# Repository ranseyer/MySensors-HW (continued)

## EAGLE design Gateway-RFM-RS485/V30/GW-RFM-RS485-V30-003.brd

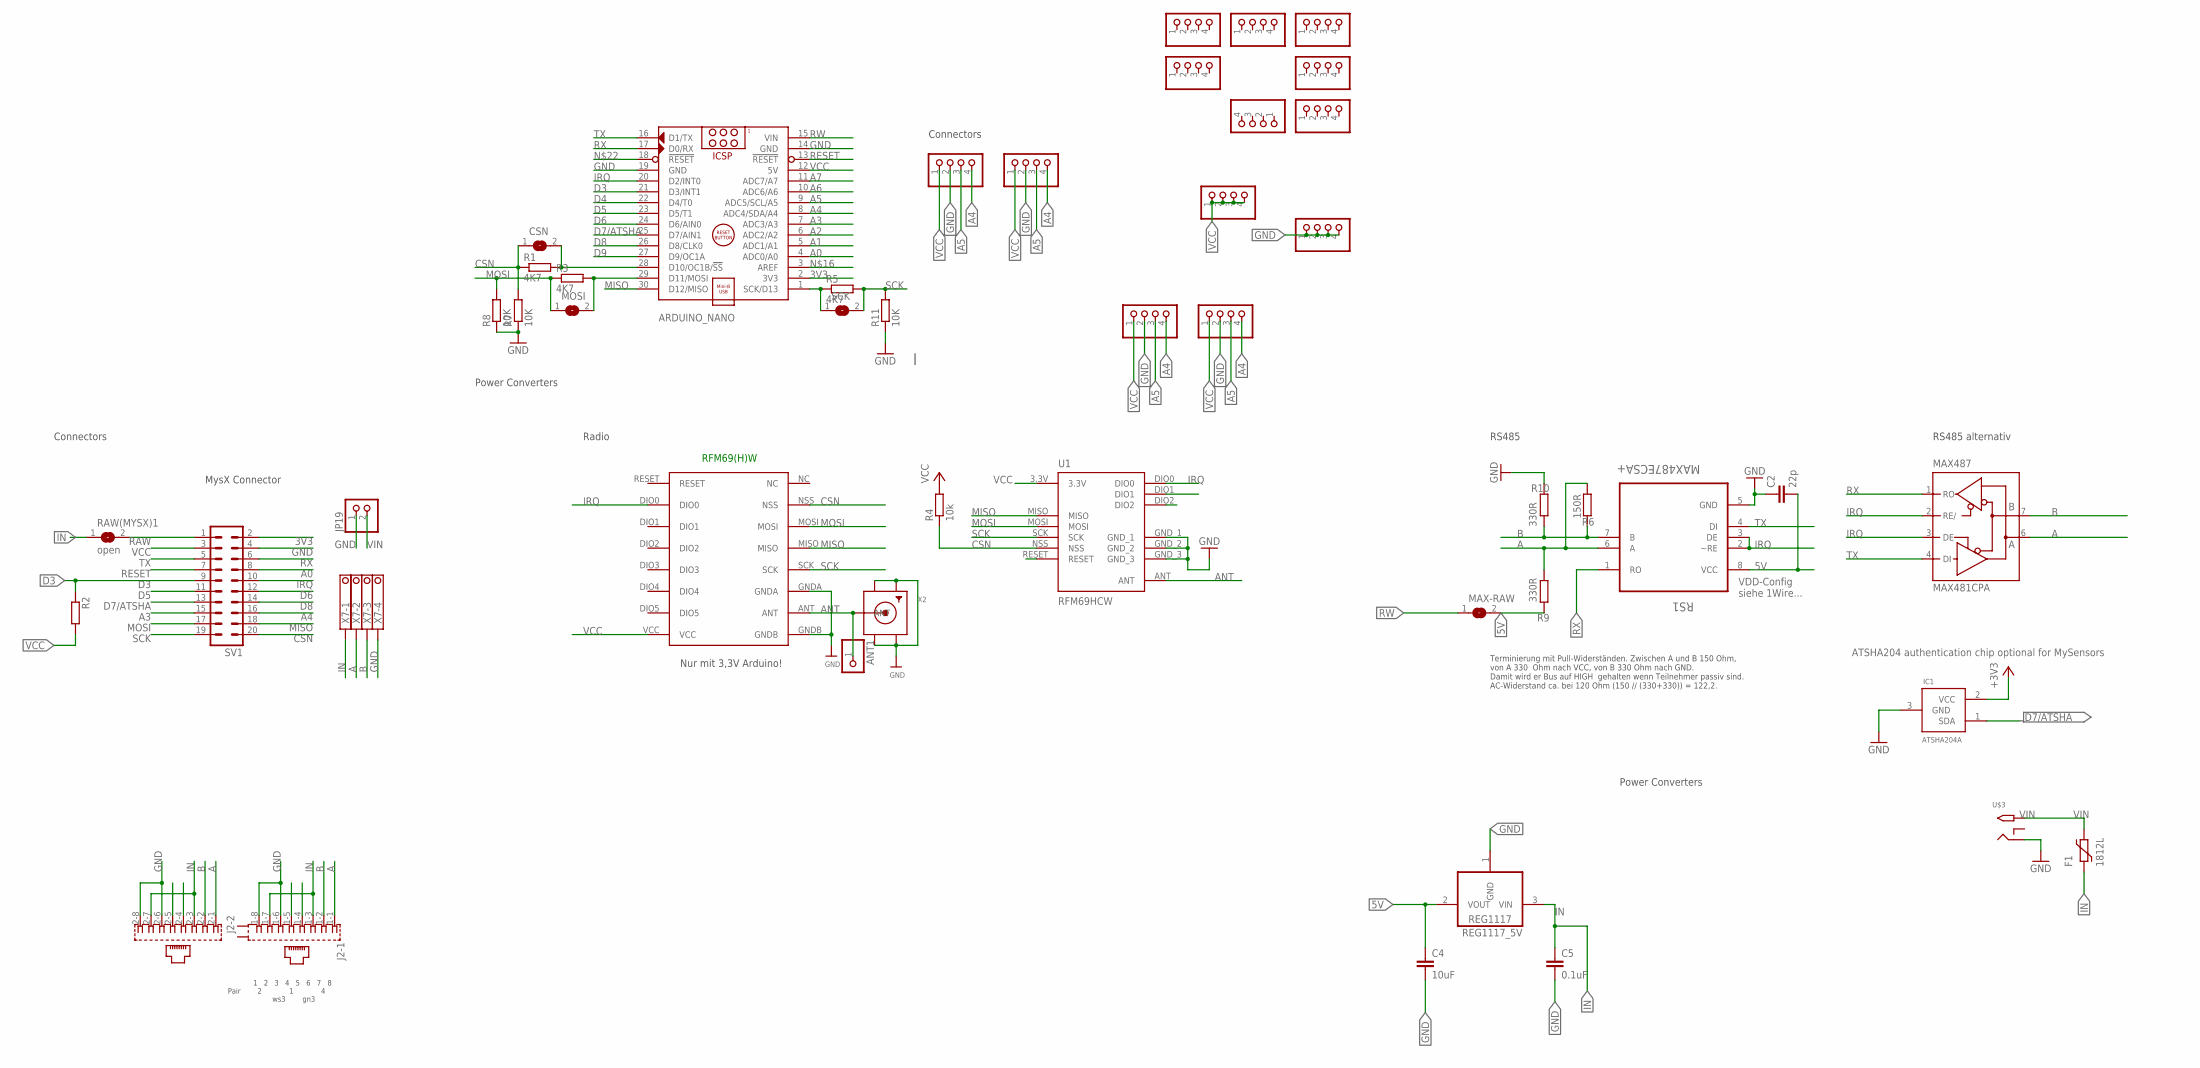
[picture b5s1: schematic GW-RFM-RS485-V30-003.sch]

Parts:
ANT1: PINHD-1X1; 1X01
ARDUINO_NANO: ARDUINO_NANO_OHNE-BOHR; ARDUINO_NANO
C2: 22p; C0805
C4: 10uF; C1210
C5: 0.1uF; C1206
CSN: SJ
F1: 1812L
IC1: ATSHA204A; SOT23
J2: 557570-1
JP1, JP2, JP3, JP4, JP5, JP6, JP7, JP10, JP11, JP12, JP15, JP17, JP18: PINHD-1X04_2.54-S; 1X04-S
JP19: PINHD-1X2; 1X02
MAX487: MAX481CPA; DIL08
MAX-RAW: SJ
MOSI: SJ
R1, R3, R5: 4K7; M0805
R2: R-EU_R0805; R0805
R4: 10k; M0805
R6: 150R; R0805
R7, R8, R11: 10K; M0805
R9, R10: 330R; R0805
RAW(MYSX)1: open; SJ
REG1117_5V: REG1117; SOT223
RFM69W: RFM69HW; RFM
RS1: MAX487ECSA+; SOIC127P600X175-8N
SCK: SJ
SV1: MA10-2
U1: RFM69HCW; RFM69HCW-XXXS2
U$3: 2.1MMJACKTHM; PJ-102A
X2: SMACONNECTOR_EDGE; SMA_EDGELAUNCH
X7: 1751264

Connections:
3V3: ARDUINO_NANO.2 (3V3), SV1.2
5V: C2.2, C4.1, MAX-RAW.2, R9.1, REG1117_5V.2 (VOUT), RS1.8 (VCC)
A: J2.1-1 (1), J2.2-1 (1), MAX487.6 (A), R6.1, R9.2, RS1.6 (A), X7.2
A0: ARDUINO_NANO.4 (ADC0/A0), SV1.8
A1: ARDUINO_NANO.5 (ADC1/A1)
A2: ARDUINO_NANO.6 (ADC2/A2)
A3: ARDUINO_NANO.7 (ADC3/A3), SV1.15
A4: ARDUINO_NANO.8 (ADC4/SDA/A4), JP6.4, JP10.4, JP17.4, JP18.4, SV1.16
A5: ARDUINO_NANO.9 (ADC5/SCL/A5), JP6.3, JP10.3, JP17.3, JP18.3
A6: ARDUINO_NANO.10 (ADC6/A6)
A7: ARDUINO_NANO.11 (ADC7/A7)
ANT: ANT1.1, RFM69W.ANT, U1.ANT, X2.P (ANT)
B: J2.1-2 (2), J2.2-2 (2), MAX487.7 (B), R6.2, R10.1, RS1.7 (B), X7.3
CSN: CSN.1, R1.1, R4.1, R7.2, RFM69W.NSS, SV1.20, U1.NSS
D3: ARDUINO_NANO.21 (D3/INT1), R2.1, SV1.9
D4: ARDUINO_NANO.22 (D4/T0)
D5: ARDUINO_NANO.23 (D5/T1), SV1.11
D6: ARDUINO_NANO.24 (D6/AIN0), SV1.12
D7/ATSHA: ARDUINO_NANO.25 (D7/AIN1), IC1.1 (SDA), SV1.13
D8: ARDUINO_NANO.26 (D8/CLK0), SV1.14
D9: ARDUINO_NANO.27 (D9/OC1A)
GND: ARDUINO_NANO.14 (GND), ARDUINO_NANO.19 (GND), C2.1, C4.2, C5.2, IC1.3 (GND), J2.1-6 (6), J2.1-8 (8), J2.2-6 (6), J2.2-8 (8), JP1.1, JP1.2, JP1.3, JP1.4, JP6.2, JP10.2, JP17.2, JP18.2, JP19.1, MAX487.5 (GND), R7.1, R8.1, R10.2, R11.1, REG1117_5V.1 (GND), RFM69W.GNDA, RFM69W.GNDB, RS1.5 (GND), SV1.4, U1.GND_1, U1.GND_2, U1.GND_3, U$3.RING, X2.GND@1 (GND4), X2.GND@2 (GND3), X2.GND@3 (GND2), X2.GND@4 (GND1), X7.4
IN: C5.1, F1.P$1 (1), J2.1-3 (3), J2.1-7 (7), J2.2-3 (3), J2.2-7 (7), RAW(MYSX)1.1, REG1117_5V.3 (VIN), X7.1
IRQ: ARDUINO_NANO.20 (D2/INT0), RFM69W.DIO0, RS1.2 (~RE), RS1.3 (DE), SV1.10, U1.DIO0
MISO: ARDUINO_NANO.30 (D12/MISO), RFM69W.MISO, SV1.18, U1.MISO
MOSI: MOSI.1, R3.1, R8.2, RFM69W.MOSI, SV1.17, U1.MOSI
unnamed: ARDUINO_NANO.1 (SCK/D13), R5.1, SCK.1
unnamed: ARDUINO_NANO.28 (D10/OC1B/!SS), CSN.2, R1.2
unnamed: ARDUINO_NANO.29 (D11/MOSI), MOSI.2, R3.2
RAW: RAW(MYSX)1.2, SV1.1
RESET: ARDUINO_NANO.13 (!RESET), SV1.7
RW: ARDUINO_NANO.15 (VIN), MAX-RAW.1
RX: ARDUINO_NANO.17 (D0/RX), RS1.1 (RO), SV1.6
SCK: R5.2, R11.2, RFM69W.SCK, SCK.2, SV1.19, U1.SCK
TX: ARDUINO_NANO.16 (D1/TX), RS1.4 (DI), SV1.5
VCC: ARDUINO_NANO.12 (5V), IC1.2 (VCC), JP3.1, JP3.2, JP3.3, JP3.4, JP6.1, JP10.1, JP17.1, JP18.1, MAX487.8 (VCC), R2.2, R4.2, RFM69W.VCC, SV1.3, U1.3.3V
VIN: F1.P$2 (2), JP19.2, U$3.TIP

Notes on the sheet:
RFM69(H)W
Nur mit 3,3V Arduino!
Radio
1 2 3 4 5 6 7 8 Pair 2 1 4 ws3 gn3
Power Converters
ATSHA204 authentication chip optional for MySensors
RS485
VDD-Config siehe 1Wire...
Terminierung mit Pull-Widerständen. Zwischen A und B 150 Ohm, von A 330 Ohm nach VCC, von B 330 Ohm nach GND. Damit wird er Bus auf HIGH gehalten wenn Teilnehmer passiv sind. AC-Widerstand ca. bei 120 Ohm (150 // (330+330)) = 122,2.
RS485 alternativ
Connectors
MysX Connector

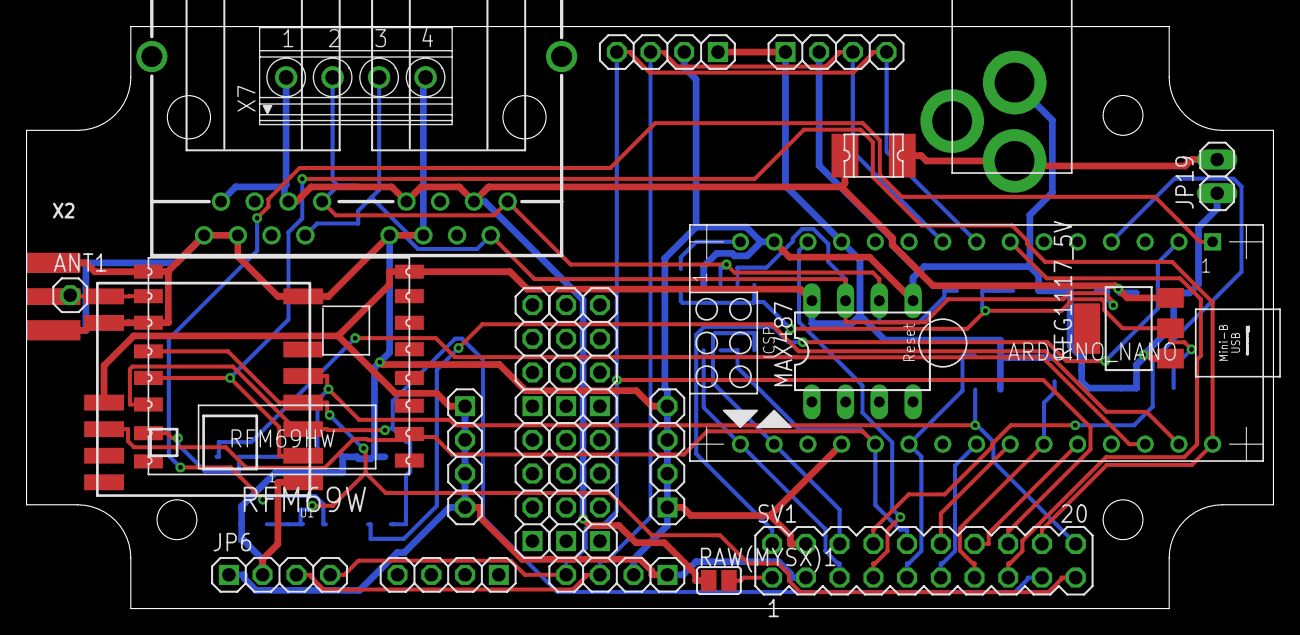
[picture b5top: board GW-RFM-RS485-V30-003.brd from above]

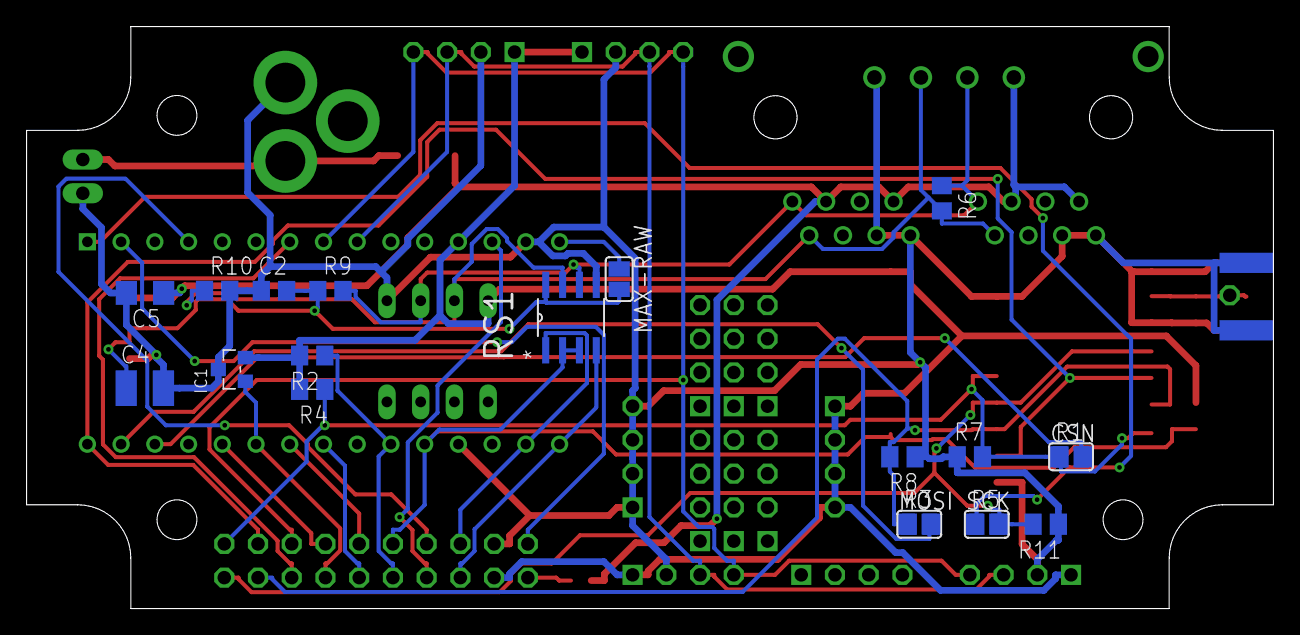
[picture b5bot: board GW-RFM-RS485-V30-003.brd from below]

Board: 2 copper layers, 93.9 x 43.8 mm, 47 parts (20 on the bottom side), 31 nets.

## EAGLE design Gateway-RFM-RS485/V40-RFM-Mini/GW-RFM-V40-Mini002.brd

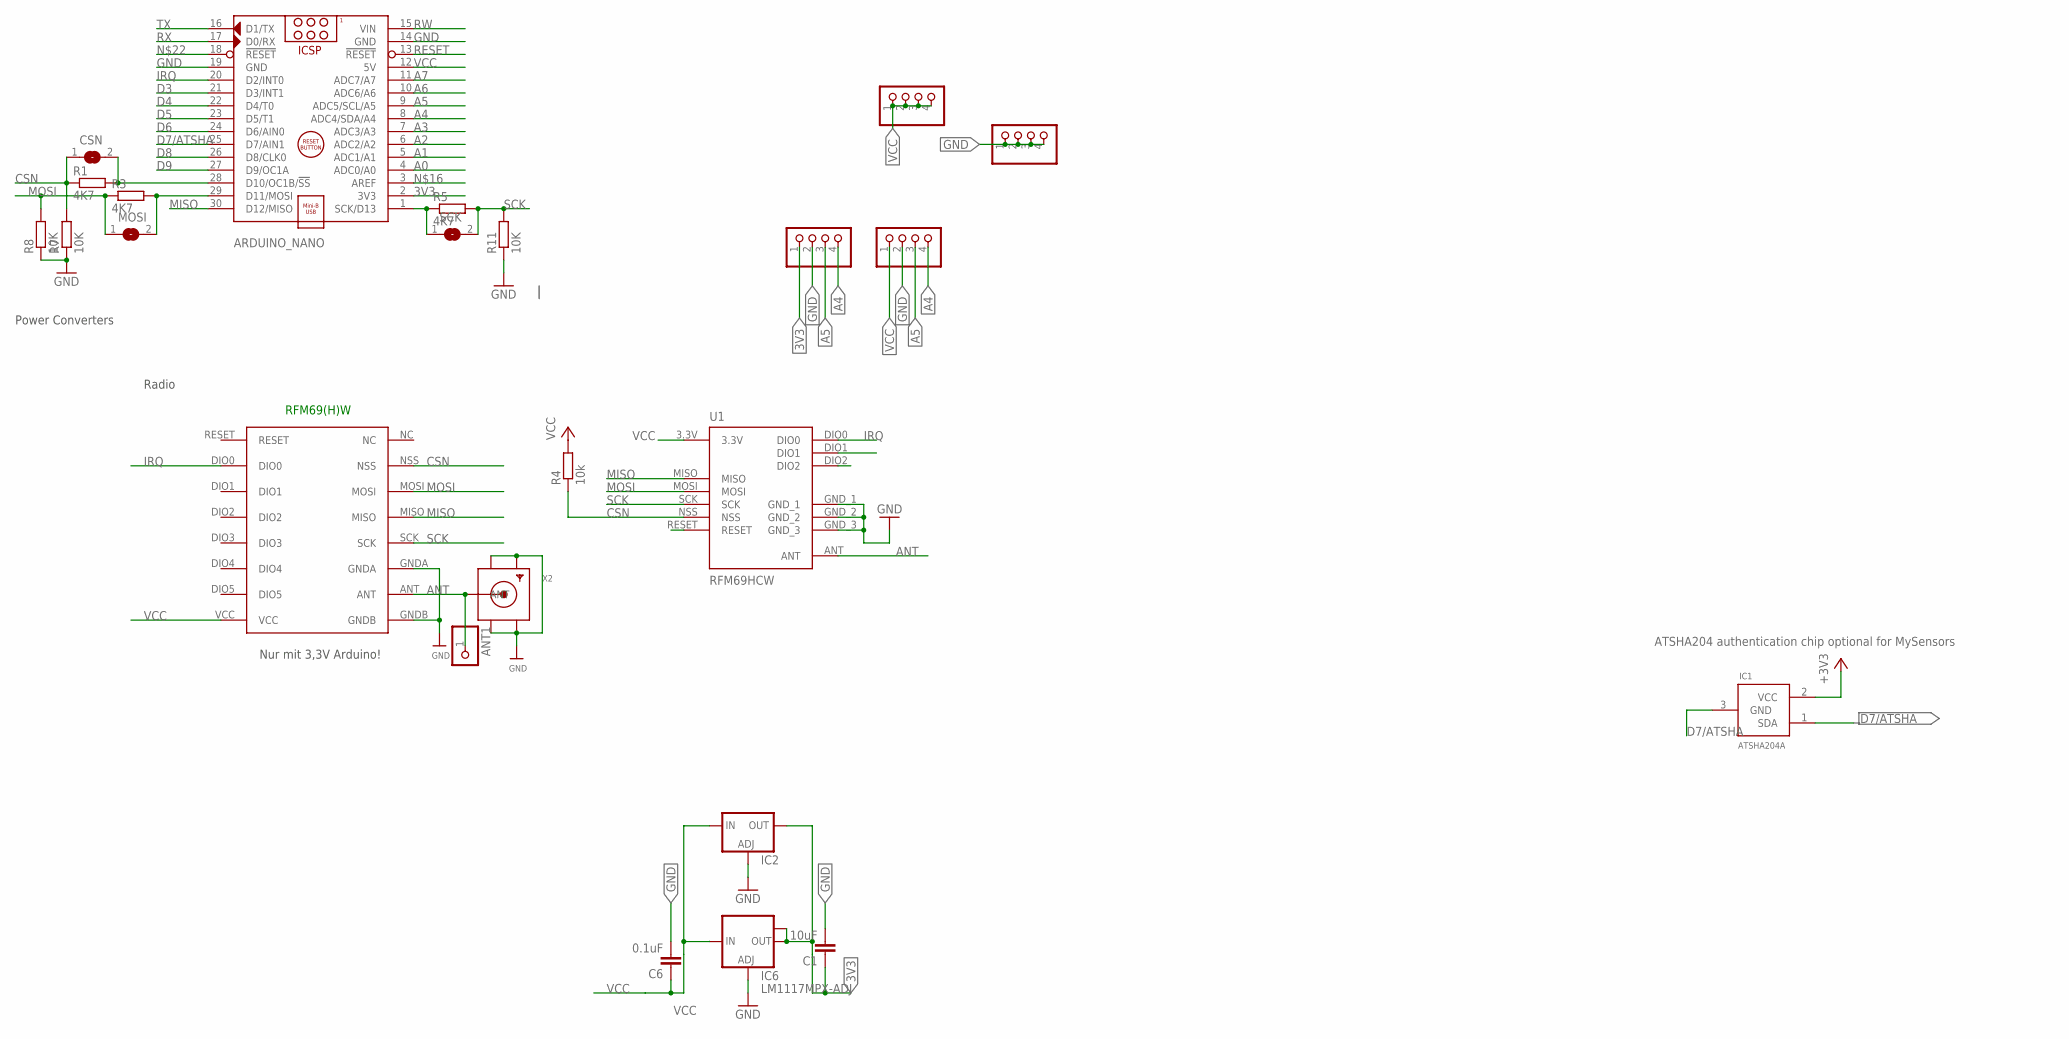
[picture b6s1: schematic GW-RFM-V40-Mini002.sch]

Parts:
ANT1: PINHD-1X1; 1X01
ARDUINO_NANO: ARDUINO_NANO_OHNE-BOHR; ARDUINO_NANO
C1: 10uF; C1210
C6: 0.1uF; C1206
CSN: SJ
IC1: ATSHA204A; SOT23
IC2: LD117ADT50TR; DPACK
IC6: LM1117MPX-ADJ; SOT223
JP1, JP3, JP17, JP18: PINHD-1X04_2.54-S; 1X04-S
MOSI: SJ
R1, R3, R5: 4K7; M0805
R4: 10k; M0805
R7, R8, R11: 10K; M0805
RFM69W: RFM69HW; RFM
SCK: SJ
U1: RFM69HCW; RFM69HCW-XXXS2
X2: SMACONNECTOR_EDGE; SMA_EDGELAUNCH

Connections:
3V3: ARDUINO_NANO.2 (3V3), C1.1, IC2.4 (OUT), IC6.2 (OUT), IC6.TAB (OUT1), JP17.1
A0: ARDUINO_NANO.4 (ADC0/A0)
A1: ARDUINO_NANO.5 (ADC1/A1)
A2: ARDUINO_NANO.6 (ADC2/A2)
A3: ARDUINO_NANO.7 (ADC3/A3)
A4: ARDUINO_NANO.8 (ADC4/SDA/A4), JP17.4, JP18.4
A5: ARDUINO_NANO.9 (ADC5/SCL/A5), JP17.3, JP18.3
A6: ARDUINO_NANO.10 (ADC6/A6)
A7: ARDUINO_NANO.11 (ADC7/A7)
ANT: ANT1.1, RFM69W.ANT, U1.ANT, X2.P (ANT)
CSN: CSN.1, R1.1, R4.1, R7.2, RFM69W.NSS, U1.NSS
D3: ARDUINO_NANO.21 (D3/INT1)
D4: ARDUINO_NANO.22 (D4/T0)
D5: ARDUINO_NANO.23 (D5/T1)
D6: ARDUINO_NANO.24 (D6/AIN0)
D7/ATSHA: ARDUINO_NANO.25 (D7/AIN1), IC1.1 (SDA), IC1.3 (GND)
D8: ARDUINO_NANO.26 (D8/CLK0)
D9: ARDUINO_NANO.27 (D9/OC1A)
GND: ARDUINO_NANO.14 (GND), ARDUINO_NANO.19 (GND), C1.2, C6.2, IC2.1 (ADJ), IC6.1 (ADJ), JP1.1, JP1.2, JP1.3, JP1.4, JP17.2, JP18.2, R7.1, R8.1, R11.1, RFM69W.GNDA, RFM69W.GNDB, U1.GND_1, U1.GND_2, U1.GND_3, X2.GND@1 (GND4), X2.GND@2 (GND3), X2.GND@3 (GND2), X2.GND@4 (GND1)
IRQ: ARDUINO_NANO.20 (D2/INT0), RFM69W.DIO0, U1.DIO0
MISO: ARDUINO_NANO.30 (D12/MISO), RFM69W.MISO, U1.MISO
MOSI: MOSI.1, R3.1, R8.2, RFM69W.MOSI, U1.MOSI
unnamed: ARDUINO_NANO.1 (SCK/D13), R5.1, SCK.1
unnamed: ARDUINO_NANO.28 (D10/OC1B/!SS), CSN.2, R1.2
unnamed: ARDUINO_NANO.29 (D11/MOSI), MOSI.2, R3.2
RESET: ARDUINO_NANO.13 (!RESET)
RW: ARDUINO_NANO.15 (VIN)
RX: ARDUINO_NANO.17 (D0/RX)
SCK: R5.2, R11.2, RFM69W.SCK, SCK.2, U1.SCK
TX: ARDUINO_NANO.16 (D1/TX)
VCC: ARDUINO_NANO.12 (5V), C6.1, IC1.2 (VCC), IC2.3 (IN), IC6.3 (IN), JP3.1, JP3.2, JP3.3, JP3.4, JP18.1, R4.2, RFM69W.VCC, U1.3.3V

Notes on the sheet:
RFM69(H)W
Nur mit 3,3V Arduino!
Radio
ATSHA204 authentication chip optional for MySensors
Power Converters

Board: 2 copper layers, 24 parts (17 on the bottom side), 15 nets, no tracks yet.
